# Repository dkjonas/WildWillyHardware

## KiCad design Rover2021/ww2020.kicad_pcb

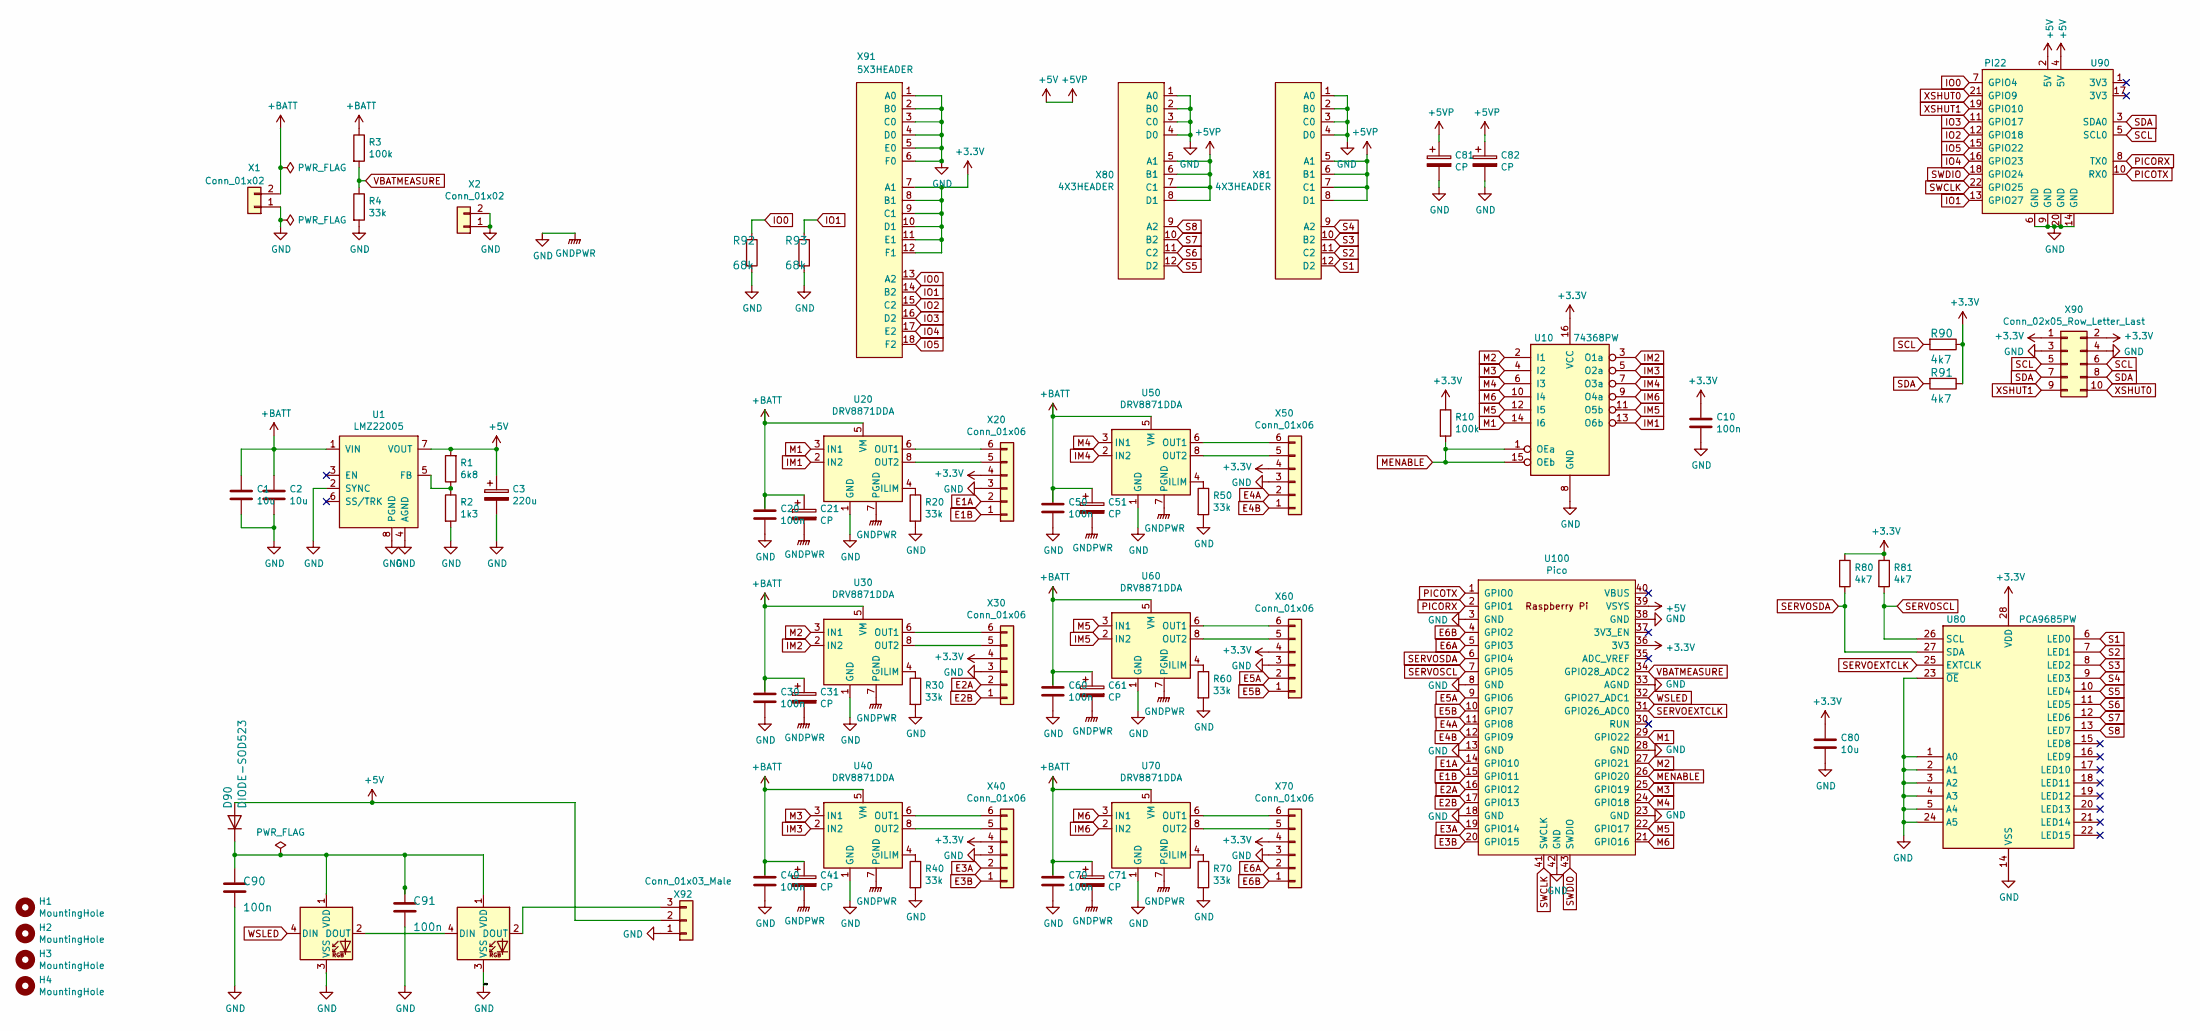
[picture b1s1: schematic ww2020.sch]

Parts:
C1, C2: 10u; C_1206_3216Metric_Pad1.33x1.80mm_HandSolder
C3: 220u; CP_Elec_6.3x7.7
C10, C20, C30, C40, C50, C60, C70, C90, C91: 100n; C_0805_2012Metric_Pad1.18x1.45mm_HandSolder
C21, C31, C41, C51, C61, C71: CP; CP_Radial_D5.0mm_P2.50mm
C80: 10u; C_0805_2012Metric_Pad1.18x1.45mm_HandSolder
C81, C82: CP; CP_Radial_D6.3mm_P2.50mm
D90: DIODE-SOD523; D_SOD-523
D91, D92: WS2812B5050; LED_WS2812B_PLCC4_5.0x5.0mm_P3.2mm
H1, H2, H3, H4: MountingHole; MountingHole_2.7mm_M2.5_Pad_Via
R1: 6k8; R_0805_2012Metric_Pad1.20x1.40mm_HandSolder
R2: 1k3; R_0805_2012Metric_Pad1.20x1.40mm_HandSolder
R3, R10: 100k; R_0805_2012Metric_Pad1.20x1.40mm_HandSolder
R4: 33k; R_0805_2012Metric_Pad1.20x1.40mm_HandSolder
R20, R30, R40, R50, R60, R70: 33k; C_0805_2012Metric_Pad1.18x1.45mm_HandSolder
R80, R81, R90, R91: 4k7; R_0805_2012Metric_Pad1.20x1.40mm_HandSolder
R92, R93: 68k; R_0805_2012Metric_Pad1.20x1.40mm_HandSolder
U1: LMZ22005; 7TO-PMOD
U10: 74368PW; TSSOP-16_4.4x5mm_P0.65mm
U20, U30, U40, U50, U60, U70: DRV8871DDA; Texas_HTSOP-8-1EP_3.9x4.9mm_P1.27mm_EP2.95x4.9mm_Mask2.4x3.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
U80: PCA9685PW; TSSOP-28_4.4x9.7mm_P0.65mm
U90: PI22; PinSocket_2x11_P2.54mm_Vertical
U100: Pico; RPi_Pico_SMD_TH
X1: Conn_01x02; AMASS_XT60PW-M
X2: Conn_01x02; PinHeader_1x02_P2.54mm_Vertical
X20, X30, X40, X50, X60, X70: Conn_01x06; JST_PH_B6B-PH-K_1x06_P2.00mm_Vertical
X80, X81: 4X3HEADER; PinHeader_3x04_P2.54mm_Vertical
X90: Conn_02x05_Row_Letter_Last; PinHeader_2x05_P2.54mm_Vertical_SMD
X91: 5X3HEADER; PinHeader_3x06_P2.54mm_Vertical
X92: Conn_01x03_Male; PinHeader_1x03_P2.54mm_Vertical

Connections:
+3V3: C10.1, C80.1, R10.1, R80.1, R81.1, R90.1, R91.1, U10.16 (VCC), U80.28 (VDD), U100.36 (3V3), X20.4, X30.4, X40.4, X50.4, X60.4, X70.4, X90.1, X90.2, X91.7 (A1), X91.8 (B1), X91.9 (C1), X91.10 (D1), X91.11 (E1), X91.12 (F1)
+5V: C3.1, C81.1, C82.1, D90.2 (A), R1.2, U1.7 (VOUT), U90.2 (5V), U90.4 (5V), U100.39 (VSYS), X80.5 (A1), X80.6 (B1), X80.7 (C1), X80.8 (D1), X81.5 (A1), X81.6 (B1), X81.7 (C1), X81.8 (D1), X92.2
+BATT: C1.1, C2.1, C20.1, C21.1, C30.1, C31.1, C40.1, C41.1, C50.1, C51.1, C60.1, C61.1, C70.1, C71.1, R3.1, U1.1 (VIN), U20.5 (VM), U30.5 (VM), U40.5 (VM), U50.5 (VM), U60.5 (VM), U70.5 (VM), X1.2
E1A: U100.14 (GPIO10), X20.2
E1B: U100.15 (GPIO11), X20.1
E2A: U100.16 (GPIO12), X30.2
E2B: U100.17 (GPIO13), X30.1
E3A: U100.19 (GPIO14), X40.2
E3B: U100.20 (GPIO15), X40.1
E4A: U100.11 (GPIO8), X50.2
E4B: U100.12 (GPIO9), X50.1
E5A: U100.9 (GPIO6), X60.2
E5B: U100.10 (GPIO7), X60.1
E6A: U100.5 (GPIO3), X70.2
E6B: U100.4 (GPIO2), X70.1
GND: C1.2, C2.2, C3.2, C10.2, C20.2, C21.2, C30.2, C31.2, C40.2, C41.2, C50.2, C51.2, C60.2, C61.2, C70.2, C71.2, C80.2, C81.2, C82.2, C90.2, C91.2, D91.3 (VSS), D92.3 (VSS), R2.2, R4.2, R20.2, R30.2, R40.2, R50.2, R60.2, R70.2, R92.2, R93.2, U1.2 (SYNC), U1.4 (AGND), U1.8 (PGND), U10.8 (GND), U20.1 (GND), U20.7 (PGND), U20.9 (GND), U30.1 (GND), U30.7 (PGND), U30.9 (GND), U40.1 (GND), U40.7 (PGND), U40.9 (GND), U50.1 (GND), U50.7 (PGND), U50.9 (GND), U60.1 (GND), U60.7 (PGND), U60.9 (GND), U70.1 (GND), U70.7 (PGND), U70.9 (GND), U80.1 (A0), U80.2 (A1), U80.3 (A2), U80.4 (A3), U80.5 (A4), U80.14 (VSS), U80.23 (~OE), U80.24 (A5), U90.6 (GND), U90.9 (GND), U90.14 (GND), U90.20 (GND), U100.3 (GND), U100.8 (GND), U100.13 (GND), U100.18 (GND), U100.23 (GND), U100.28 (GND), U100.33 (AGND), U100.38 (GND), U100.42 (GND), X1.1, X2.1, X2.2, X20.3, X30.3, X40.3, X50.3, X60.3, X70.3, X80.1 (A0), X80.2 (B0), X80.3 (C0), X80.4 (D0), X81.1 (A0), X81.2 (B0), X81.3 (C0), X81.4 (D0), X90.3, X90.4, X91.1 (A0), X91.2 (B0), X91.3 (C0), X91.4 (D0), X91.5 (E0), X91.6 (F0), X92.1
IM1: U10.13 (O6b), U20.2 (IN2)
IM2: U10.3 (O1a), U30.2 (IN2)
IM3: U10.5 (O2a), U40.2 (IN2)
IM4: U10.7 (O3a), U50.2 (IN2)
IM5: U10.11 (O5b), U60.2 (IN2)
IM6: U10.9 (O4a), U70.2 (IN2)
IO0: R92.1, U90.7 (GPIO4), X91.13 (A2)
IO1: R93.1, U90.13 (GPIO27), X91.14 (B2)
IO2: U90.12 (GPIO18), X91.15 (C2)
IO3: U90.11 (GPIO17), X91.16 (D2)
IO4: U90.16 (GPIO23), X91.17 (E2)
IO5: U90.15 (GPIO22), X91.18 (F2)
M1: U10.14 (I6), U20.3 (IN1), U100.29 (GPIO22)
M2: U10.2 (I1), U30.3 (IN1), U100.27 (GPIO21)
M3: U10.4 (I2), U40.3 (IN1), U100.25 (GPIO19)
M4: U10.6 (I3), U50.3 (IN1), U100.24 (GPIO18)
M5: U10.12 (I5), U60.3 (IN1), U100.22 (GPIO17)
M6: U10.10 (I4), U70.3 (IN1), U100.21 (GPIO16)
MENABLE: R10.2, U10.1 (OEa), U10.15 (OEb), U100.26 (GPIO20)
unnamed: C90.1, C91.1, D90.1 (K), D91.1 (VDD), D92.1 (VDD)
unnamed: D91.2 (DOUT), D92.4 (DIN)
unnamed: D92.2 (DOUT), X92.3
unnamed: R1.1, R2.1, U1.5 (FB)
unnamed: R20.1, U20.4 (ILIM)
unnamed: R30.1, U30.4 (ILIM)
unnamed: R40.1, U40.4 (ILIM)
unnamed: R50.1, U50.4 (ILIM)
unnamed: R60.1, U60.4 (ILIM)
unnamed: R70.1, U70.4 (ILIM)
unnamed: U20.6 (OUT1), X20.6
unnamed: U20.8 (OUT2), X20.5
unnamed: U30.6 (OUT1), X30.6
unnamed: U30.8 (OUT2), X30.5
unnamed: U40.6 (OUT1), X40.6
unnamed: U40.8 (OUT2), X40.5
unnamed: U50.6 (OUT1), X50.6
unnamed: U50.8 (OUT2), X50.5
unnamed: U60.6 (OUT1), X60.6
unnamed: U60.8 (OUT2), X60.5
unnamed: U70.6 (OUT1), X70.6
unnamed: U70.8 (OUT2), X70.5
PICORX: U90.8 (TX0), U100.2 (GPIO1)
PICOTX: U90.10 (RX0), U100.1 (GPIO0)
S1: U80.6 (LED0), X81.12 (D2)
S2: U80.7 (LED1), X81.11 (C2)
S3: U80.8 (LED2), X81.10 (B2)
S4: U80.9 (LED3), X81.9 (A2)
S5: U80.10 (LED4), X80.12 (D2)
S6: U80.11 (LED5), X80.11 (C2)
S7: U80.12 (LED6), X80.10 (B2)
S8: U80.13 (LED7), X80.9 (A2)
SCL: R90.2, U90.5 (SCL0), X90.5, X90.6
SDA: R91.2, U90.3 (SDA0), X90.7, X90.8
SERVOEXTCLK: U80.25 (EXTCLK), U100.31 (GPIO26_ADC0)
SERVOSCL: R81.2, U80.26 (SCL), U100.7 (GPIO5)
SERVOSDA: R80.2, U80.27 (SDA), U100.6 (GPIO4)
SWCLK: U90.22 (GPIO25), U100.41 (SWCLK)
SWDIO: U90.18 (GPIO24), U100.43 (SWDIO)
VBATMEASURE: R3.2, R4.1, U100.34 (GPIO28_ADC2)
WSLED: D91.4 (DIN), U100.32 (GPIO27_ADC1)
XSHUT0: U90.21 (GPIO9), X90.10
XSHUT1: U90.19 (GPIO10), X90.9

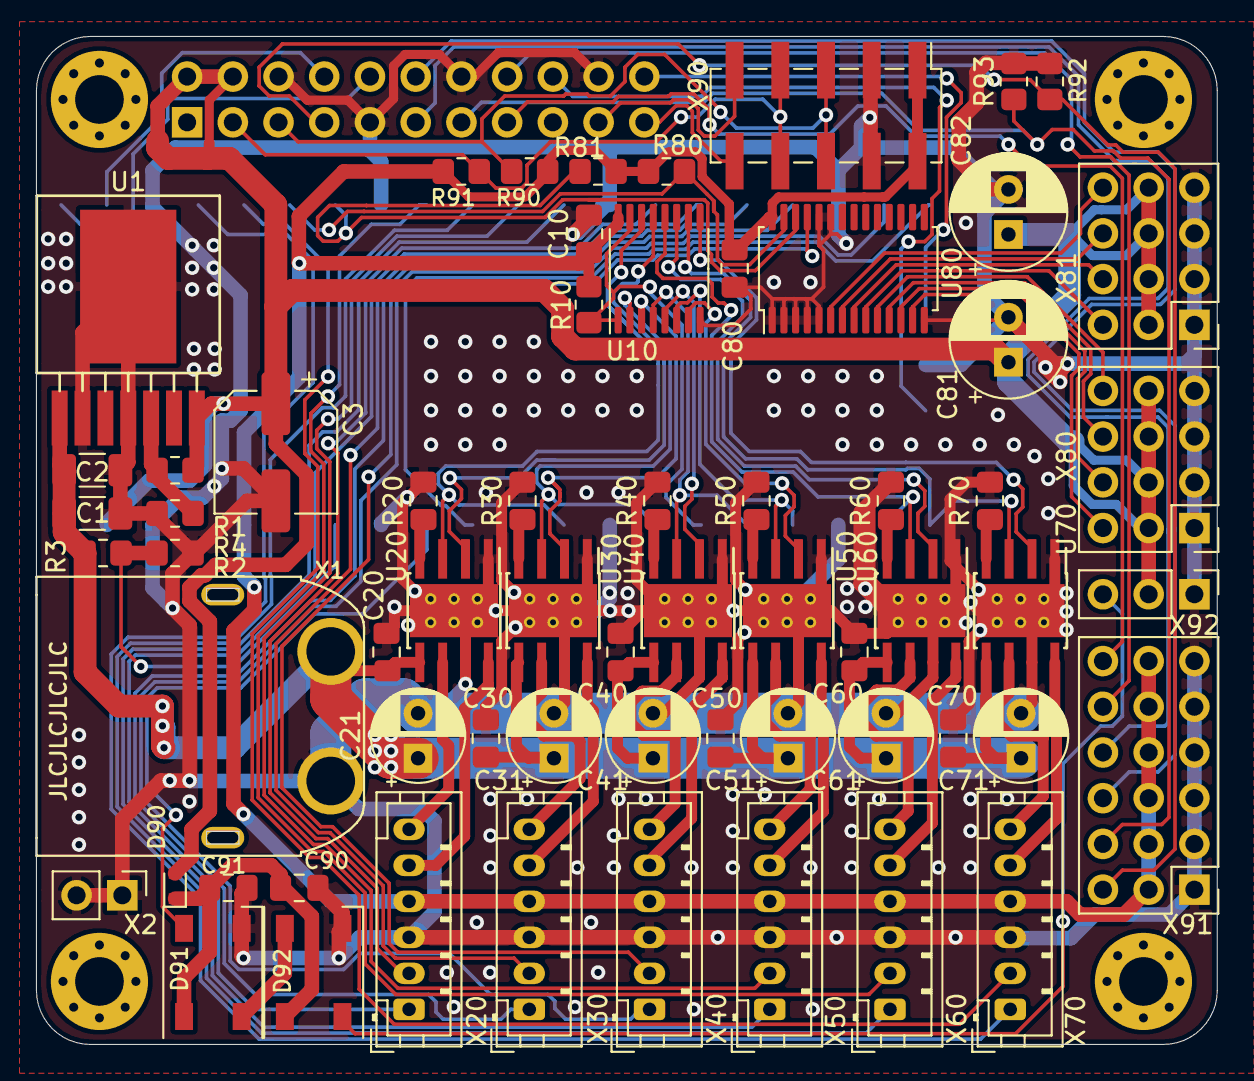
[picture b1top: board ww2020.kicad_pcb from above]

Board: 2 copper layers, 65.6 x 56.0 mm, 69 parts (0 on the bottom side), 78 nets.

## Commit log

2021-08-15 Import of PCB produced 6-6-2021
